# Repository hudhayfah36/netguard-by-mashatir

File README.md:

<div align="center">

# NetGuard by Mashatir

**A small device. More control over your home network.**

A USB-C-powered, open-source DNS filtering device built around the ESP32-S3.

**Local control · No account · No subscription**

[The idea](#the-idea) · [How it works](#how-it-works) · [Hardware](#hardware) · [Project status](#project-status) · [Contributing](CONTRIBUTING.md)

</div>

<div align="center"><em>Enclosure concept render; final hardware design is in progress.</em></div>

## The idea

NetGuard is designed to give your home network a local DNS filtering device. Configure your router to give its address to your devices, and DNS queries can be checked against your rules before connections are made. Phones, laptops, TVs, consoles, and IoT devices can benefit without installing an app on each one.

The product vision is a pocket-sized device configured with a companion mobile app: Bluetooth for initial setup, then local-network communication. No cloud dashboard, account, or subscription is intended.

### Designed for everyday control

| Feature | Product vision |
| --- | --- |
| **Network-wide filtering** | Block requests to known advertising, tracking, and malware domains. |
| **Your rules** | Block or allow domains and set time-based access rules. |
| **Per-device controls** | Apply rules to devices using their local network addresses. |
| **Blocklist and allowlist modes** | Choose between blocking known domains or allowing only specified domains. |
| **Local setup and control** | Pair over Bluetooth, then use the mobile app on the local network. |
| **Open source** | Share the firmware, hardware designs, and companion app. |

> **Development status:** This table describes the product vision, not a list of features verified in the current firmware. See [Project status](#project-status) before using it as a purchase or deployment guide.

## How it works

1. Configure the router's DHCP settings to give clients NetGuard's local IP address as their DNS server.
2. Client devices send DNS queries directly to NetGuard.
3. NetGuard checks applicable domain rules and schedules; blocked requests receive `NXDOMAIN`.
4. The current firmware forwards permitted queries to upstream resolvers. Fully local DNS resolution is a project goal, **not** a feature of the current firmware.

Per-device rules depend on clients sending DNS directly to NetGuard. If a router proxies DNS queries, requests can appear to come from the router rather than individual devices.

## Hardware

<div align="center">
  
  <p><em>NetGuard PCB render — enclosure design is in progress.</em></p>
</div>

The board measures **55 × 40 mm** and includes Wi-Fi, Bluetooth, USB-C power, four indicator LEDs, and three physical buttons. Explore the [KiCad PCB layout](hardware/pcb/netguard_compact_r2.kicad_pcb) or the [full-size PCB render](images/netguard_pcb_render.png).

## Project status

NetGuard is being prepared for crowdfunding. The PCB layout is available in this repository; the enclosure and companion mobile app are in progress.

The current firmware includes a DNS filter, global blocks, schedules, per-device profiles, and a local HTTP API. It does not serve a web frontend in the current source tree. Bluetooth provisioning, allowlist mode, and fully local DNS resolution are part of the intended direction and are not implemented here yet. The mobile app and PCB schematic are not included in this repository.

The [v0.1.0 release](release/README.md) predates the current API-only source and includes the earlier dashboard-based firmware. Check the release notes and [flashing guide](docs/FLASHING.md) before flashing.

## Network limits

DNS filtering is not a complete firewall. Manually configured DNS, encrypted DNS, IPv6 DNS, VPNs, proxies, and direct IP connections can bypass it unless the network applies additional controls. Keep the local HTTP API on a trusted network and do not expose it directly to the internet.

## Build and contribute

The firmware is an ESP-IDF project targeting the ESP32-S3. See the [flashing guide](docs/FLASHING.md), [contribution guidelines](CONTRIBUTING.md), and [release history](CHANGELOG.md).

Contributions to firmware, hardware documentation, testing, and the planned mobile experience are welcome.

## License

This repository is available under the [MIT License](LICENSE).

<div align="center">

**Built for local control. Designed to be open.**

</div>

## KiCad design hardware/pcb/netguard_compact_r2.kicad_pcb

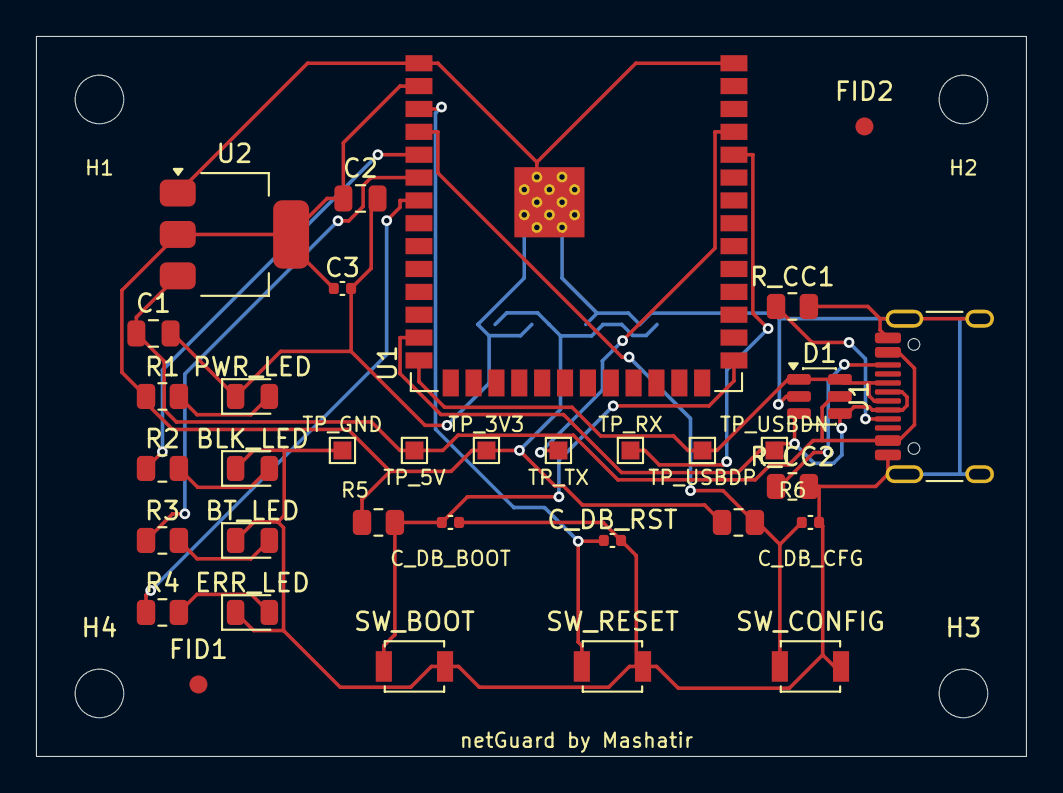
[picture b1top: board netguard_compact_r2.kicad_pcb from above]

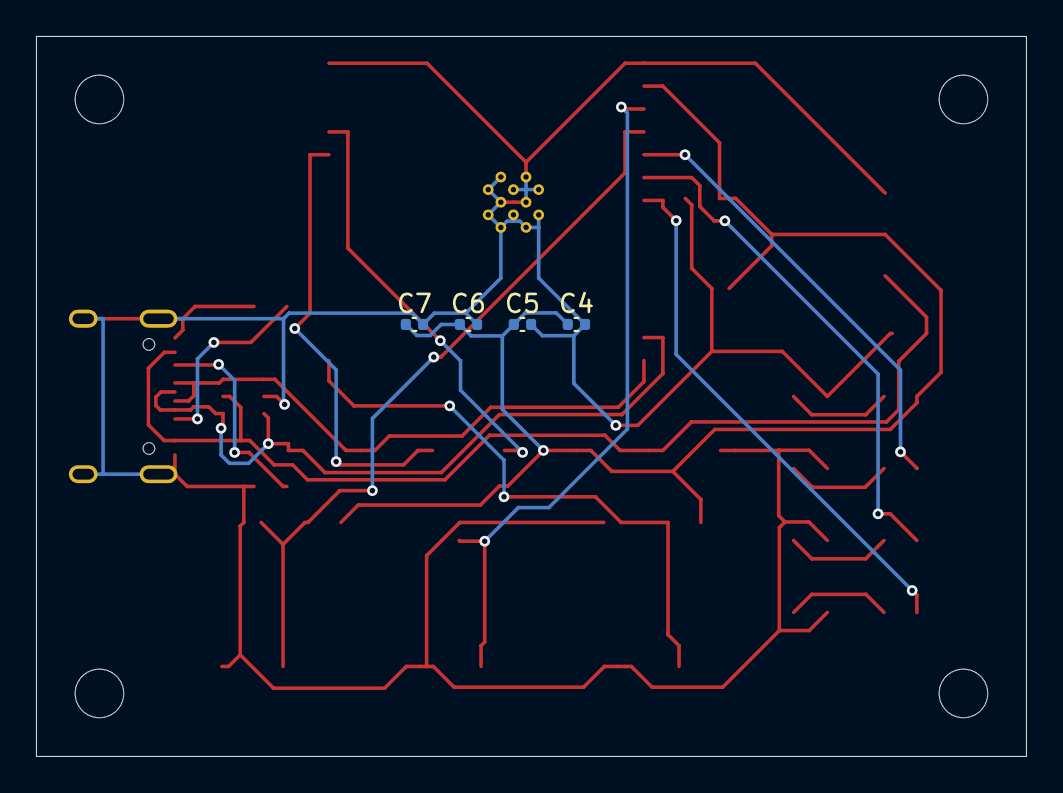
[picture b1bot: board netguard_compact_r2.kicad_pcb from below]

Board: 2 copper layers, 55.0 x 40.0 mm, 42 parts (4 on the bottom side), 19 nets.

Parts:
BLK_LED: LED_Yellow; LED_0805_2012Metric
BT_LED: LED_Blue; LED_0805_2012Metric
C1, C2: 10uF/10V; C_0805_2012Metric
C3, C4, C5, C6, C7: 100nF; C_0402_1005Metric
C_DB_BOOT: 100nF; C_0402_1005Metric
C_DB_CFG: 100nF; C_0402_1005Metric
C_DB_RST: 100nF; C_0402_1005Metric
D1: USBLC6-2SC6; SOT-23-6
ERR_LED: LED_Red; LED_0805_2012Metric
FID1, FID2: Fiducial; Fiducial_1mm_Mask2mm
H1, H2, H3, H4: M2.5; MountingHole_2.7mm_M2.5
J1: USB_C_HRO_TYPE-C-31-M-12; USB_C_Receptacle_HRO_TYPE-C-31-M-12
PWR_LED: LED_Green; LED_0805_2012Metric
R1, R2, R3, R4: 330R; R_0805_2012Metric
R5, R6: 10k; R_0805_2012Metric
R_CC1, R_CC2: 5k1; R_0805_2012Metric
SW_BOOT: B3U-1000P; SW_SPST_B3U-1000P
SW_CONFIG: B3U-1000P; SW_SPST_B3U-1000P
SW_RESET: B3U-1000P; SW_SPST_B3U-1000P
TP_3V3: +3V3; TestPoint_Pad_1.0x1.0mm
TP_5V: +5V; TestPoint_Pad_1.0x1.0mm
TP_GND: GND; TestPoint_Pad_1.0x1.0mm
TP_RX: UART_RX; TestPoint_Pad_1.0x1.0mm
TP_TX: UART_TX; TestPoint_Pad_1.0x1.0mm
TP_USBDN: USB_DN; TestPoint_Pad_1.0x1.0mm
TP_USBDP: USB_DP; TestPoint_Pad_1.0x1.0mm
U1: ESP32-S3-WROOM-1
U2: AMS1117-3.3; SOT-223-3_TabPin2

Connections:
+3V3: C2.1, C3.1, C4.1, C5.1, C6.1, C7.1, R1.1, R5.1, R6.1, TP_3V3.1, U1.2, U2.2
+5V: C1.1, D1.5, J1.A4, J1.A9, J1.B4, J1.B9, TP_5V.1, U2.3
BOOT_BTN: C_DB_BOOT.1, R5.2, SW_BOOT.1, U1.27
CONFIG_BTN: C_DB_CFG.1, R6.2, SW_CONFIG.1, U1.4
GND: BLK_LED.1, BT_LED.1, C1.2, C2.2, C3.2, C4.2, C5.2, C6.2, C7.2, C_DB_BOOT.2, C_DB_CFG.2, C_DB_RST.2, D1.2, ERR_LED.1, J1.A1, J1.A12, J1.B1, J1.B12, J1.SH, PWR_LED.1, R_CC1.2, R_CC2.2, SW_BOOT.2, SW_CONFIG.2, SW_RESET.2, TP_GND.1, U1.1, U1.40, U1.41, U2.1
LED_BLK: R2.1, U1.5
LED_BLK_A: BLK_LED.2, R2.2
LED_BT: R3.1, U1.6
LED_BT_A: BT_LED.2, R3.2
LED_ERR: R4.1, U1.7
LED_ERR_A: ERR_LED.2, R4.2
LED_PWR_A: PWR_LED.2, R1.2
RESET_BTN: C_DB_RST.1, SW_RESET.1, U1.3
UART_RX: TP_RX.1, U1.36
UART_TX: TP_TX.1, U1.37
USB_CC1: J1.A5, R_CC1.1
USB_CC2: J1.B5, R_CC2.1
USB_DN: D1.3, D1.4, J1.A7, J1.B7, TP_USBDN.1, U1.13
USB_DP: D1.1, D1.6, J1.A6, J1.B6, TP_USBDP.1, U1.14

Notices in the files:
hardware/pcb/netguard_compact_r2.kicad_pcb:
OSHW — CC-BY-SA 4.0
